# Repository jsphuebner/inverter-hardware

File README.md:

# inverter-hardware
Eagle schematics of inverter main board, sensor boards and gate drivers

# License
Attribution-ShareAlike 4.0 International
https://creativecommons.org/licenses/by-sa/4.0/legalcode

You musn't change the copyright info (J. Huebner and openinverter.org) on the silkscreen in size location or content.

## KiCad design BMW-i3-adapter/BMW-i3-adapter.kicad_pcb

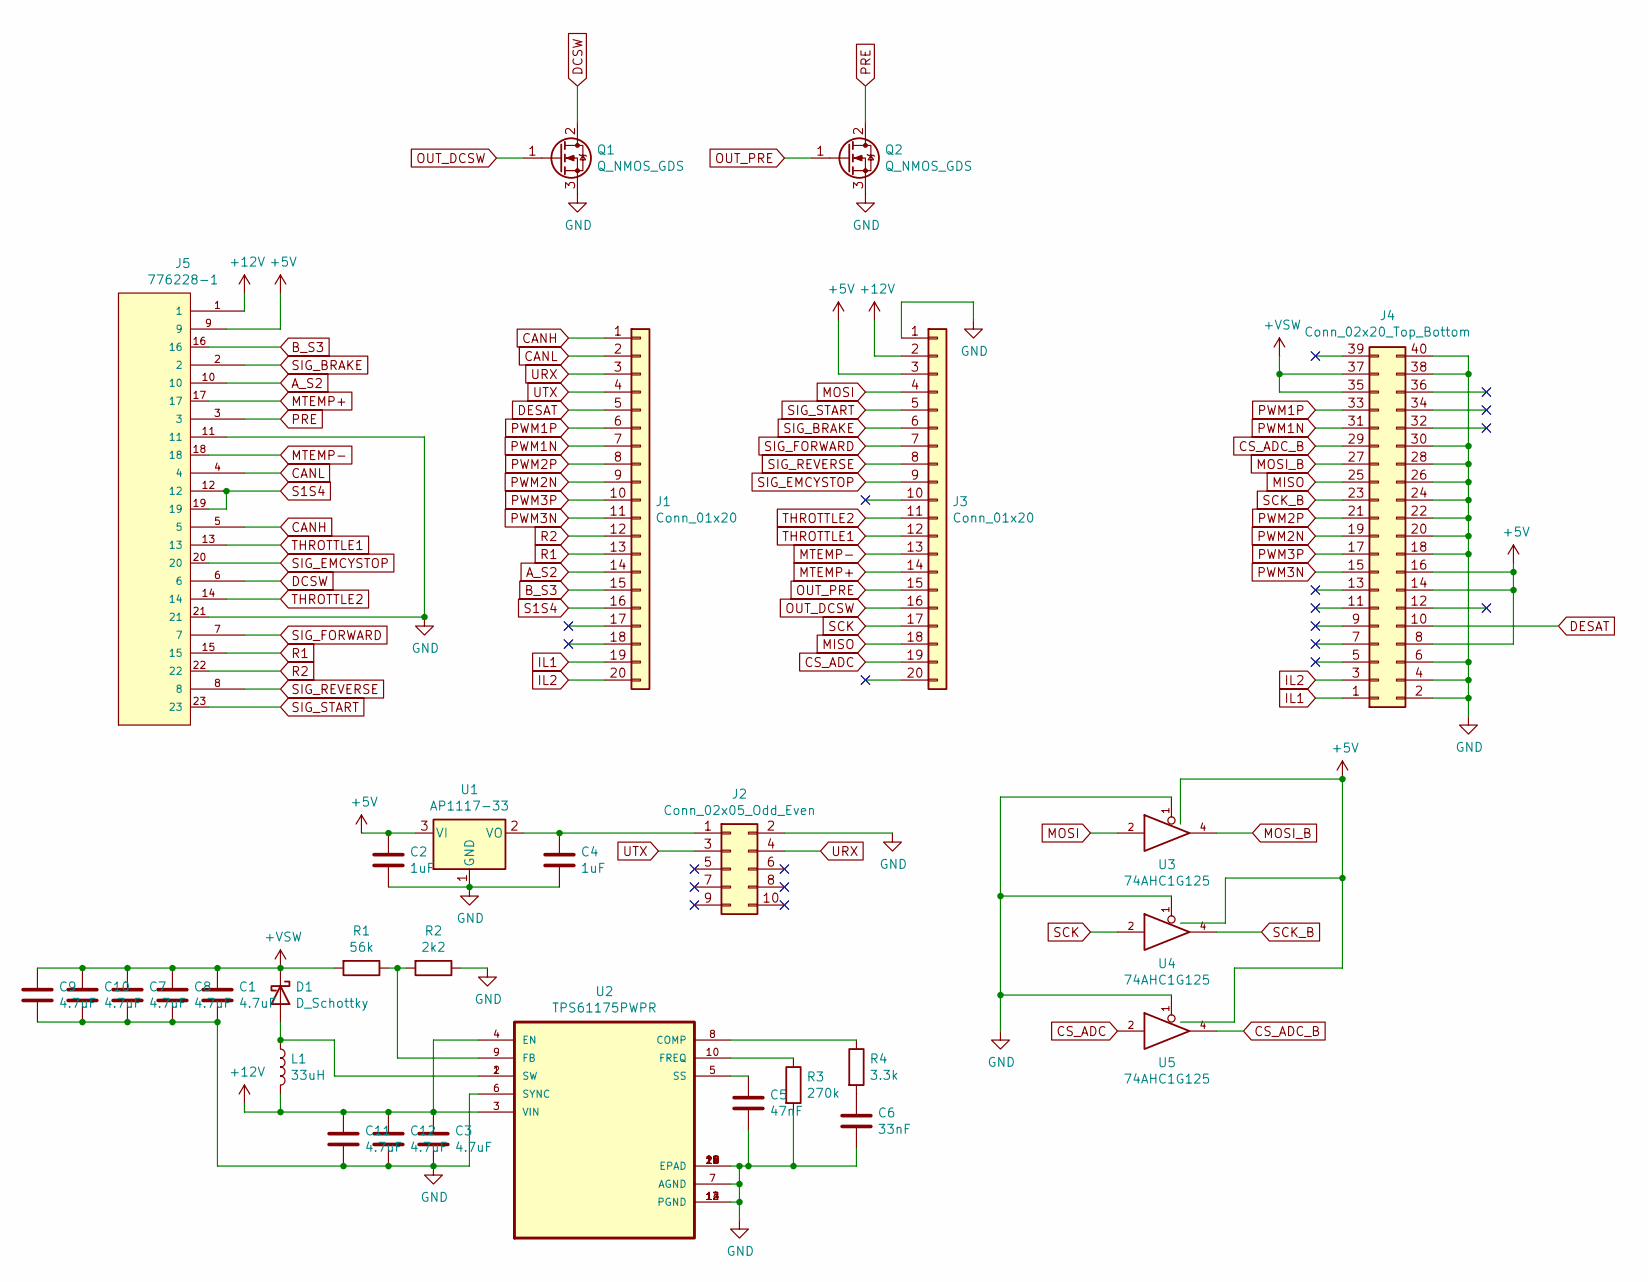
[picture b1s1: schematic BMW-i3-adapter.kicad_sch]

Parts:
C1, C3, C7, C8, C9, C10, C11, C12: 4.7uF; C_1206_3216Metric
C2, C4: 1uF; C_0603_1608Metric
C5: 47nF; C_0603_1608Metric
C6: 33nF; C_0603_1608Metric
D1: D_Schottky; D_SMB
J1, J3: Conn_01x20; PinHeader_1x20_P2.54mm_Vertical
J2: Conn_02x05_Odd_Even; PinHeader_2x05_P2.54mm_Horizontal
J4: Conn_02x20_Top_Bottom; M55-7104042R
J5: 776228-1; TE_776228-1
L1: 33uH; L_10.4x10.4_H4.8
Q1, Q2: Q_NMOS_GDS; TO-263-3_TabPin2
R1: 56k; R_0603_1608Metric
R2: 2k2; R_0603_1608Metric
R3: 270k; R_0603_1608Metric
R4: 3.3k; R_0603_1608Metric
U1: AP1117-33; SOT-223-3_TabPin2
U2: TPS61175PWPR; IC_TPS27S100BPWPR
U3, U4, U5: 74AHC1G125; SOT-353_SC-70-5

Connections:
+5V: C2.1, J3.3, J4.8, J4.14, J4.16, J5.9, U1.3 (VI), U3.5 (VCC), U4.5 (VCC), U5.5 (VCC)
+12V: C3.1, C11.1, C12.1, J3.2, J5.1, L1.2, U2.3 (VIN), U2.4 (EN)
+VSW: C1.1, C7.1, C8.1, C9.1, C10.1, D1.1 (K), J4.35, J4.37, R1.2
A_S2: J1.14, J5.10
B_S3: J1.15, J5.16
CANH: J1.1, J5.5
CANL: J1.2, J5.4
CS_ADC: J3.19, U5.2
CS_ADC_B: J4.29, U5.4
DCSW: J5.6, Q1.2 (D)
DESAT: J1.5, J4.10
GND: C1.2, C2.2, C3.2, C4.2, C5.2, C6.2, C7.2, C8.2, C9.2, C10.2, C11.2, C12.2, J2.2, J3.1, J4.2, J4.4, J4.6, J4.18, J4.20, J4.22, J4.24, J4.26, J4.28, J4.30, J4.38, J4.40, J5.11, J5.21, Q1.3 (S), Q2.3 (S), R2.1, R3.2, U1.1 (GND), U2.6 (SYNC), U2.7 (AGND), U2.12 (PGND), U2.13 (PGND), U2.14 (PGND), U2.15 (EPAD), U2.16 (EPAD), U2.17 (EPAD), U2.18 (EPAD), U2.19 (EPAD), U2.20 (EPAD), U2.21 (EPAD), U3.1, U3.3 (GND), U4.1, U4.3 (GND), U5.1, U5.3 (GND)
IL1: J1.19, J4.1
IL2: J1.20, J4.3
MISO: J3.18, J4.25
MOSI: J3.4, U3.2
MOSI_B: J4.27, U3.4
MTEMP+: J3.14, J5.17
MTEMP-: J3.13, J5.18
unnamed: C4.1, J2.1, U1.2 (VO)
unnamed: C5.1, U2.5 (SS)
unnamed: C6.1, R4.2
unnamed: D1.2 (A), L1.1, U2.1 (SW), U2.2 (SW)
unnamed: R1.1, R2.2, U2.9 (FB)
unnamed: R3.1, U2.10 (FREQ)
unnamed: R4.1, U2.8 (COMP)
OUT_DCSW: J3.16, Q1.1 (G)
OUT_PRE: J3.15, Q2.1 (G)
PRE: J5.3, Q2.2 (D)
PWM1N: J1.7, J4.31
PWM1P: J1.6, J4.33
PWM2N: J1.9, J4.19
PWM2P: J1.8, J4.21
PWM3N: J1.11, J4.15
PWM3P: J1.10, J4.17
R1: J1.13, J5.15
R2: J1.12, J5.22
S1S4: J1.16, J5.12, J5.19
SCK: J3.17, U4.2
SCK_B: J4.23, U4.4
SIG_BRAKE: J3.6, J5.2
SIG_EMCYSTOP: J3.9, J5.20
SIG_FORWARD: J3.7, J5.7
SIG_REVERSE: J3.8, J5.8
SIG_START: J3.5, J5.23
THROTTLE1: J3.12, J5.13
THROTTLE2: J3.11, J5.14
URX: J1.3, J2.4
UTX: J1.4, J2.3

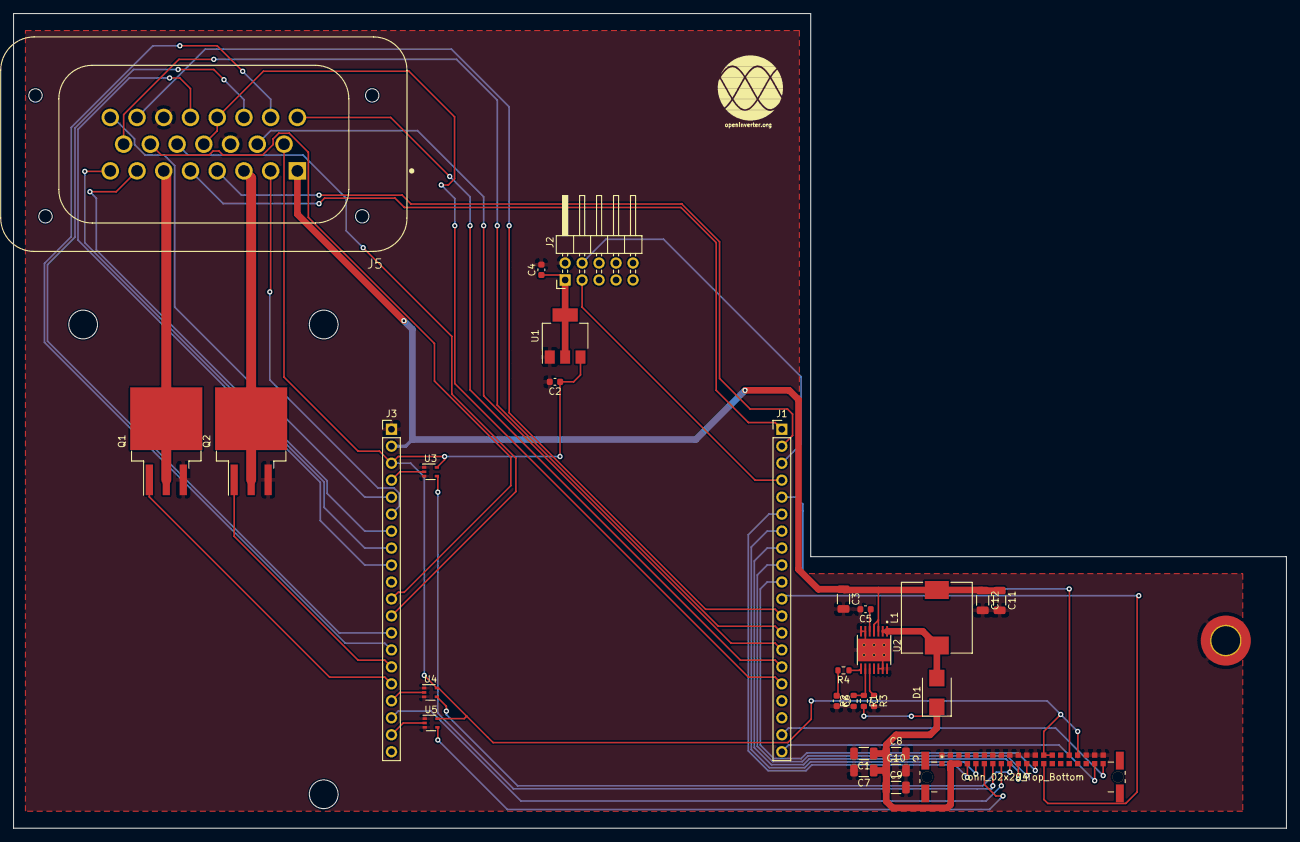
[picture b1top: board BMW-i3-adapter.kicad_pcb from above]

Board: 2 copper layers, 190.5 x 121.9 mm, 31 parts (0 on the bottom side), 49 nets.

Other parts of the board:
U$2: OI_LOGO

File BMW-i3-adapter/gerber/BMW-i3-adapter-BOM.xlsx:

Designator | Comment | Footprint | LCSC Part #
C8,C7,C1,C3,C9,C10,C11,C12 | 4.7uF | C_1206_3216Metric | C29823
C6 | 33nF | C_0603_1608Metric | C21117
D1 | D_Schottky | D_SMB | C65009
U2 | TPS61175PWPR | HTSSOP-14_EP_4.4x5.0x0.65P | C43276
J1,J3 | Conn_01x20 | PinSocket_1x20_P2.54mm_Vertical
J5 | 776228-1 | TE_776228-1
C2,C4 | 1uF | C_0603_1608Metric | C15849
C5 | 47nF | C_0603_1608Metric | C1622
J2 | Conn_02x05_Odd_Even | PinHeader_2x05_P2.54mm_Horizontal
J4 | Conn_02x20_Top_Bottom | M55-7004042R
L1 | 33uH | L_1210_3225Metric | C9936
Q1,Q2 | Q_NMOS_GDS | TO-263-3_TabPin2 | C161842
R1 | 56kΩ | R_0603_1608Metric | C23206
R2 | 2.2kΩ | R_0603_1608Metric | C4190
R3 | 270kΩ | R_0603_1608Metric | C22965
R4 | 3.3kΩ | R_0603_1608Metric | C22978
U1 | AP1117-33 | SOT-223-3_TabPin2 | C6186
U3,U4,U5 | 74AHC1G125 | SC-70-5 | C350557

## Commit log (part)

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2018-11-01 Added openinverter library
    Contains foot print for SMD mainboard. Lets you design an adapter board
2018-11-09 Changed a component value and added annotations
2018-11-10 Added credits for drawing
2018-11-30 Label corrections
    Corrected swapped labels of IC2 and IC8. Added part number of IC9
2018-12-03 Added missing part numbers
2019-01-03 Added gate driver schematics and layout
2019-05-15 Added leaf adapter design file
2020-01-03 Added openinverter V3 SMD mainboard revision 1.2
2020-01-03 Added revision info
2020-01-25 Small changed for compatibility with JLCPCBs parts library
2020-01-25 Added Gerber, BOM and placement file - NAND gate still has wrong foot print!
2020-01-25 Replaced SOT23-6 by SC70-6 foot print for IC9 Moved copyright info away from trace fixed font of silk screen
2020-06-29 New mainboard v3.4 Using TagConnect for programming Using FET for dcsw output Optimized BOM Added solder bridges for optional resistors
2020-07-15 Added Prius manufacturing files and schematic
2020-08-30 Added labels to IC7 and IC5
2021-04-08 Added phase module
2021-04-08 force .fpc crlf
2021-11-19 Updated Leaf adapter to SMT
2021-11-19 Added Leaf adapter BOM and PLC
2022-04-09 Added mini mainboard
2022-07-05 Added 10k resistor to CAN transceiver RS pin
2022-07-20 Updated pdf

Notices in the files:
BMW-i3-adapter/BMW-i3-adapter.kicad_pcb:
(c) 2021 J. Huebner
parts and their libraries:
Copyright 2016 Accelerated Designs. All rights reserved.
